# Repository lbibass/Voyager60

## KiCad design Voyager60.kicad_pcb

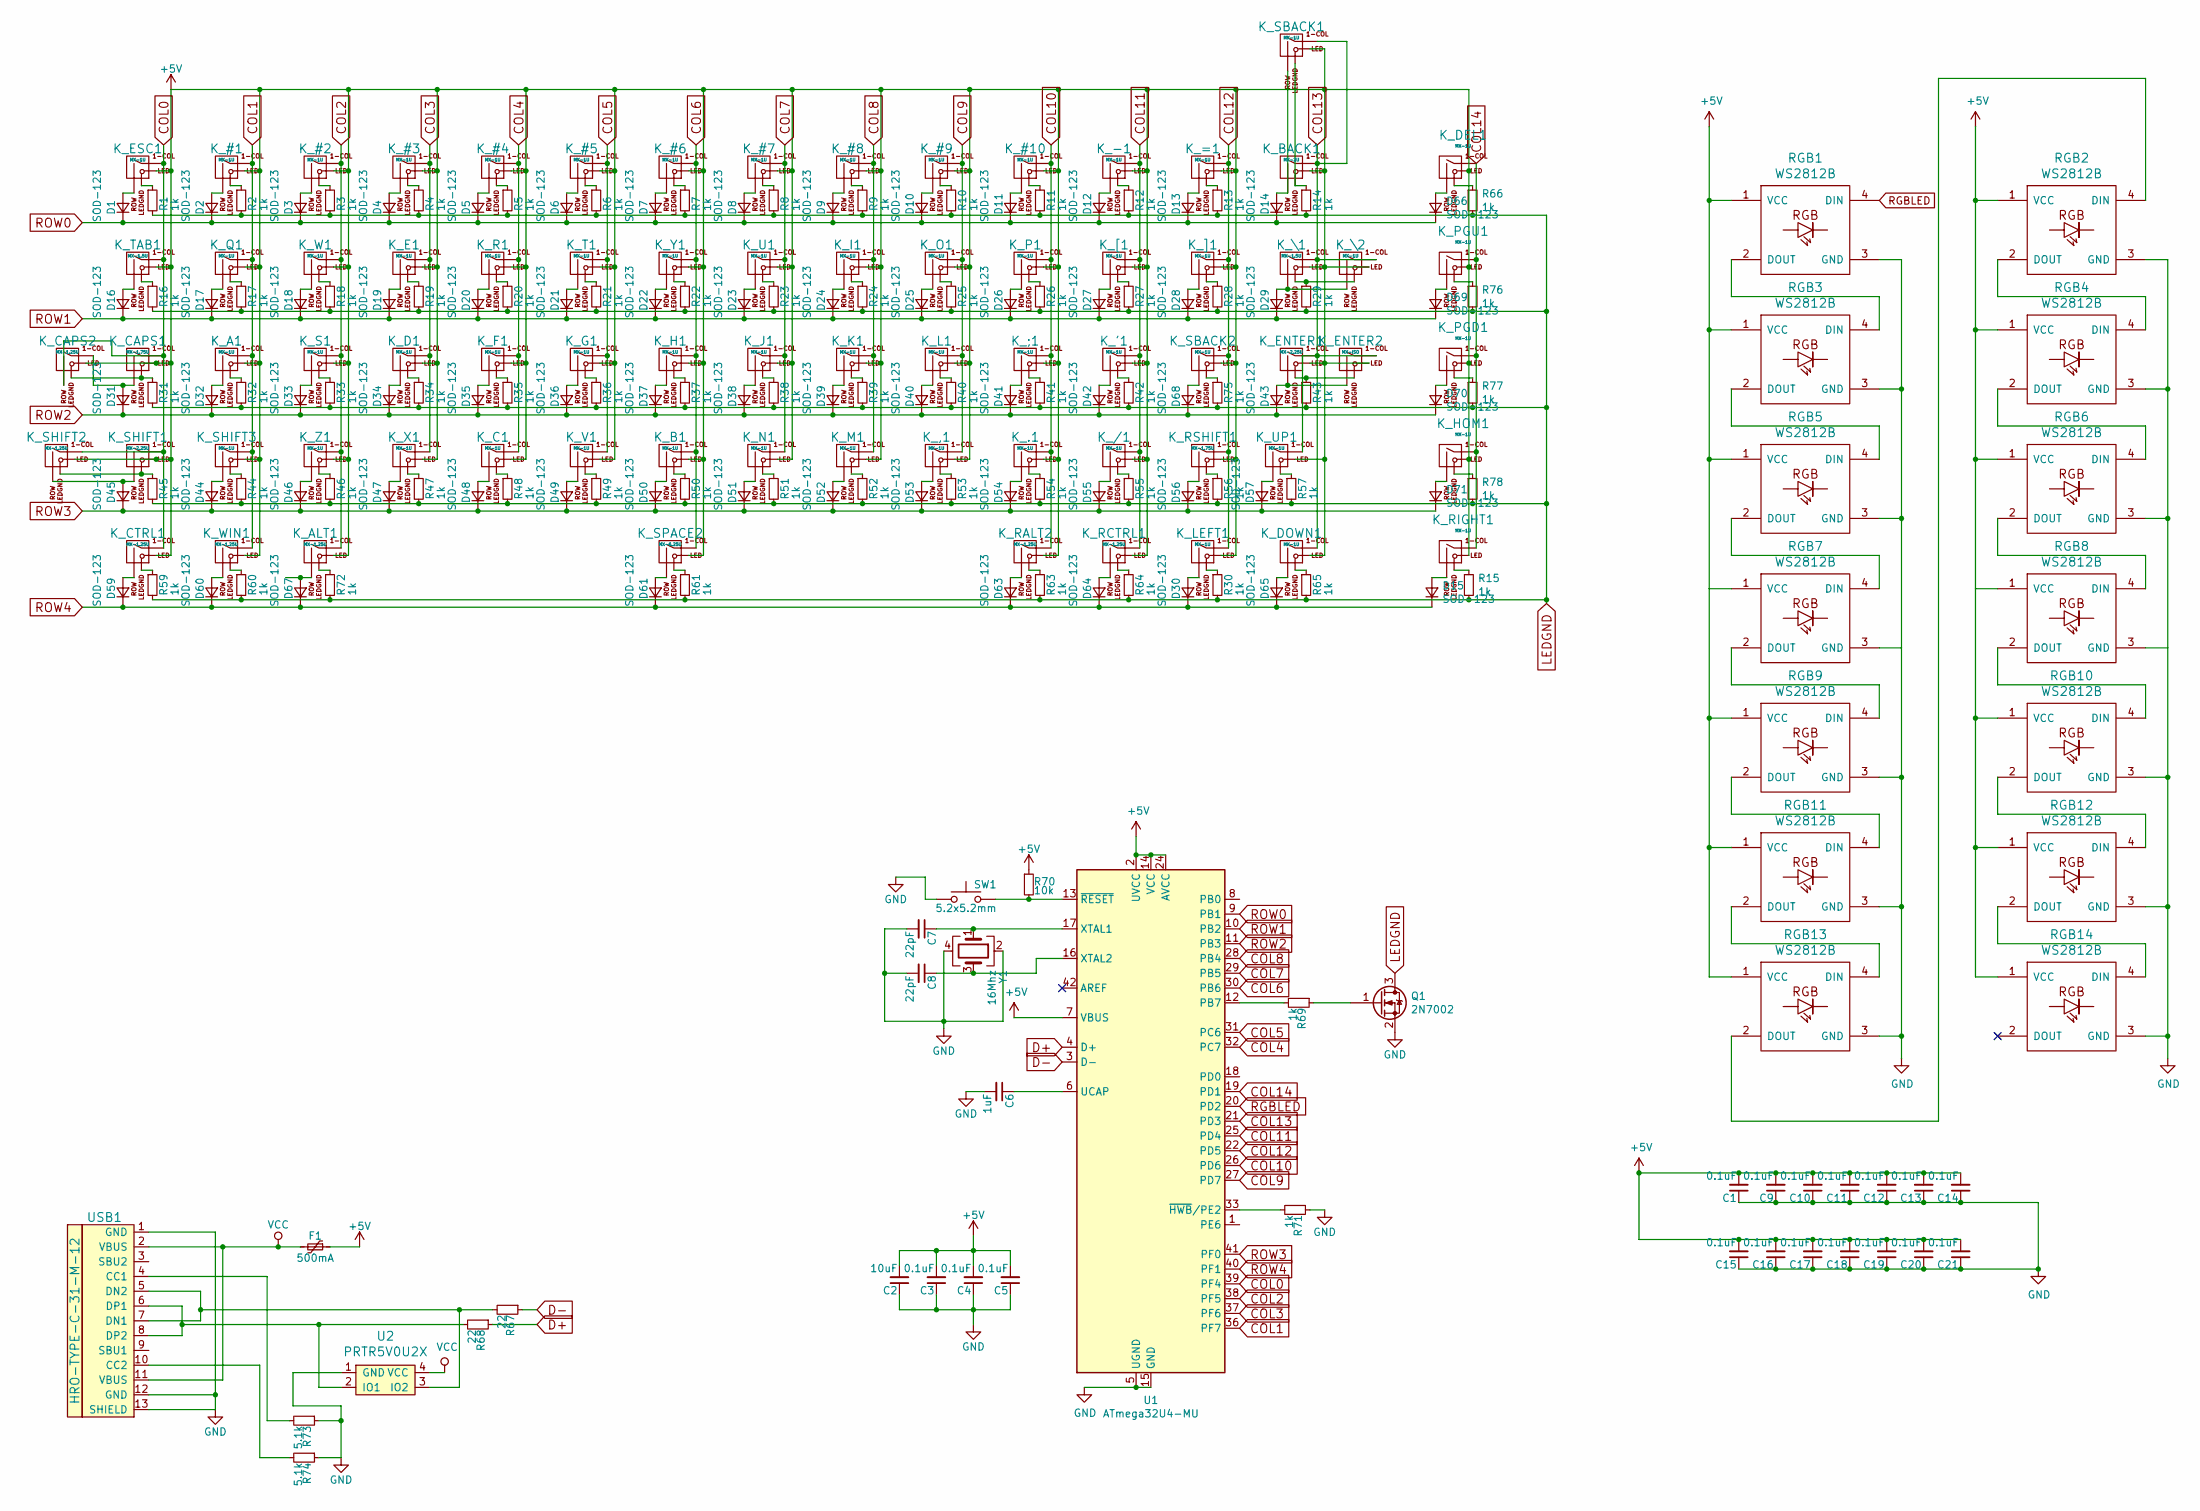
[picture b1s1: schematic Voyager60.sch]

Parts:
C1, C3, C4, C5, C9, C10, C11, C12, C13, C14, C15, C16, C17, C18, C19, C20, C21: 0.1uF; C_0603
C2: 10uF; C_0603
C6: 1uF; C_0603
C7, C8: 22pF; C_0603
D1, D2, D3, D4, D5, D6, D7, D8, D9, D10, D11, D12, D13, D14, D15, D16, D17, D18, D19, D20, D21, D22, D23, D24, D25, D26, D27, D28, D29, D30, D31, D32, D33, D34, D35, D36, D37, D38, D39, D40, D41, D42, D43, D44, D45, D46, D47, D48, D49, D50, D51, D52, D53, D54, D55, D56, D57, D59, D60, D61, D63, D64, D65, D66, D67, D68, D69, D70, D71: SOD-123; D_SOD-123
F1: 500mA; Fuse_SMD1206_Reflow
K_#1, K_#2, K_#3, K_#4, K_#5, K_#6, K_#7, K_#8, K_#9, K_#10: MX-1U
K_'1: MX-1U
K_,1: MX-1U
K_-1: MX-1U
K_.1: MX-1U
K_/1: MX-1U
K_;1: MX-1U
K_=1: MX-1U
K_A1: MX-1U
K_ALT1: MX-1.25U
K_B1: MX-1U
K_BACK1: MX-2U
K_C1: MX-1U
K_CAPS1: MX-1.75U
K_CAPS2: MX-1.25U; MX-1.25U-FLIPPED
K_CTRL1: MX-1.25U
K_D1: MX-1U
K_DEL1: MX-1U
K_DOWN1: MX-1U
K_E1: MX-1U
K_ENTER1: MX-2.25U
K_ENTER2: MX-ISO; MX-ISO-ReversedStabilizers
K_ESC1: MX-1U
K_F1: MX-1U
K_G1: MX-1U
K_H1: MX-1U
K_HOM1: MX-1U
K_I1: MX-1U
K_J1: MX-1U
K_K1: MX-1U
K_L1: MX-1U
K_LEFT1: MX-1U
K_M1: MX-1U
K_N1: MX-1U
K_O1: MX-1U
K_P1: MX-1U
K_PGD1: MX-1U
K_PGU1: MX-1U
K_Q1: MX-1U
K_R1: MX-1U
K_RALT2: MX-1.25U; MX-1.25U-FLIPPED
K_RCTRL1: MX-1.25U
K_RIGHT1: MX-1U
K_RSHIFT1: MX-1.75U
K_S1: MX-1U
K_SBACK1, K_SBACK2: MX-1U
K_SHIFT1: MX-2.25U
K_SHIFT2: MX-1.25U
K_SHIFT3: MX-1U
K_SPACE2: MX-6.25U; MX-6.25U-ReversedStabilizers
K_T1: MX-1U
K_TAB1: MX-1.5U
K_U1: MX-1U
K_UP1: MX-1U
K_V1: MX-1U
K_W1: MX-1U
K_WIN1: MX-1.25U
K_X1: MX-1U
K_Y1: MX-1U
K_Z1: MX-1U
K_[1: MX-1U
K_\1: MX-1.5U
K_\2: MX-1U
K_]1: MX-1U
Q1: 2N7002; SOT-23
R1, R2, R3, R4, R5, R6, R7, R8, R9, R10, R11, R12, R13, R14, R15, R16, R17, R18, R19, R20, R21, R22, R23, R24, R25, R26, R27, R28, R29, R30, R31, R32, R33, R34, R35, R36, R37, R38, R39, R40, R41, R42, R43, R44, R45, R46, R47, R48, R49, R50, R51, R52, R53, R54, R55, R56, R57, R59, R60, R61, R63, R64, R65, R66, R69, R71, R72, R75, R76, R77, R78: 1k; R_0805
R67, R68: 22; R_0805
R70: 10k; R_0805
R73, R74: 5.1k; R_0805
RGB1, RGB2, RGB3, RGB4, RGB5, RGB6, RGB7, RGB8, RGB9, RGB10, RGB11, RGB12, RGB13, RGB14: WS2812B
SW1: 5.2x5.2mm; SKQG-1155865
U1: ATmega32U4-MU; QFN-44-1EP_7x7mm_Pitch0.5mm
U2: PRTR5V0U2X; SOT143B
USB1: HRO-TYPE-C-31-M-12; HRO-TYPE-C-31-M-12-Assembly
Y1: 16Mhz; Crystal_SMD_3225-4pin_3.2x2.5mm

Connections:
+5V: C1.2, C2.2, C3.2, C4.2, C5.2, C9.2, C10.2, C11.2, C12.2, C13.2, C14.2, C15.2, C16.2, C17.2, C18.2, C19.2, C20.2, C21.2, F1.1, K_#1.3 (LED), K_#2.3 (LED), K_#3.3 (LED), K_#4.3 (LED), K_#5.3 (LED), K_#6.3 (LED), K_#7.3 (LED), K_#8.3 (LED), K_#9.3 (LED), K_#10.3 (LED), K_'1.3 (LED), K_,1.3 (LED), K_-1.3 (LED), K_.1.3 (LED), K_/1.3 (LED), K_;1.3 (LED), K_=1.3 (LED), K_A1.3 (LED), K_ALT1.3 (LED), K_B1.3 (LED), K_BACK1.3 (LED), K_C1.3 (LED), K_CAPS1.3 (LED), K_CAPS2.3 (LED), K_CTRL1.3 (LED), K_D1.3 (LED), K_DEL1.3 (LED), K_DOWN1.3 (LED), K_E1.3 (LED), K_ENTER1.3 (LED), K_ENTER2.3 (LED), K_ESC1.3 (LED), K_F1.3 (LED), K_G1.3 (LED), K_H1.3 (LED), K_HOM1.3 (LED), K_I1.3 (LED), K_J1.3 (LED), K_K1.3 (LED), K_L1.3 (LED), K_LEFT1.3 (LED), K_M1.3 (LED), K_N1.3 (LED), K_O1.3 (LED), K_P1.3 (LED), K_PGD1.3 (LED), K_PGU1.3 (LED), K_Q1.3 (LED), K_R1.3 (LED), K_RALT2.3 (LED), K_RCTRL1.3 (LED), K_RIGHT1.3 (LED), K_RSHIFT1.3 (LED), K_S1.3 (LED), K_SBACK1.3 (LED), K_SBACK2.3 (LED), K_SHIFT1.3 (LED), K_SHIFT2.3 (LED), K_SHIFT3.3 (LED), K_SPACE2.3 (LED), K_T1.3 (LED), K_TAB1.3 (LED), K_U1.3 (LED), K_UP1.3 (LED), K_V1.3 (LED), K_W1.3 (LED), K_WIN1.3 (LED), K_X1.3 (LED), K_Y1.3 (LED), K_Z1.3 (LED), K_[1.3 (LED), K_\1.3 (LED), K_\2.3 (LED), K_]1.3 (LED), R70.1, RGB1.1 (VCC), RGB2.1 (VCC), RGB3.1 (VCC), RGB4.1 (VCC), RGB5.1 (VCC), RGB6.1 (VCC), RGB7.1 (VCC), RGB8.1 (VCC), RGB9.1 (VCC), RGB10.1 (VCC), RGB11.1 (VCC), RGB12.1 (VCC), RGB13.1 (VCC), RGB14.1 (VCC), U1.2 (UVCC), U1.7 (VBUS), U1.14 (VCC), U1.24 (AVCC), U1.34 (VCC), U1.44 (AVCC)
COL0: K_CAPS1.1 (COL), K_CAPS2.2 (ROW), K_CTRL1.1 (COL), K_ESC1.1 (COL), K_SHIFT1.1 (COL), K_SHIFT2.1 (COL), K_TAB1.1 (COL), U1.39 (PF4)
COL1: K_#1.1 (COL), K_A1.1 (COL), K_Q1.1 (COL), K_SHIFT3.1 (COL), K_WIN1.1 (COL), U1.36 (PF7)
COL2: K_#2.1 (COL), K_ALT1.1 (COL), K_S1.1 (COL), K_W1.1 (COL), K_Z1.1 (COL), U1.38 (PF5)
COL3: K_#3.1 (COL), K_D1.1 (COL), K_E1.1 (COL), K_X1.1 (COL), U1.37 (PF6)
COL4: K_#4.1 (COL), K_C1.1 (COL), K_F1.1 (COL), K_R1.1 (COL), U1.32 (PC7)
COL5: K_#5.1 (COL), K_G1.1 (COL), K_T1.1 (COL), K_V1.1 (COL), U1.31 (PC6)
COL6: K_#6.1 (COL), K_B1.1 (COL), K_H1.1 (COL), K_SPACE2.1 (COL), K_Y1.1 (COL), U1.30 (PB6)
COL7: K_#7.1 (COL), K_J1.1 (COL), K_N1.1 (COL), K_U1.1 (COL), U1.29 (PB5)
COL8: K_#8.1 (COL), K_I1.1 (COL), K_K1.1 (COL), K_M1.1 (COL), U1.28 (PB4)
COL9: K_#9.1 (COL), K_,1.1 (COL), K_L1.1 (COL), K_O1.1 (COL), U1.27 (PD7)
COL10: K_#10.1 (COL), K_.1.1 (COL), K_;1.1 (COL), K_P1.1 (COL), K_RALT2.1 (COL), U1.26 (PD6)
COL11: K_'1.1 (COL), K_-1.1 (COL), K_/1.1 (COL), K_RCTRL1.1 (COL), K_[1.1 (COL), U1.25 (PD4)
COL12: K_=1.1 (COL), K_LEFT1.1 (COL), K_RSHIFT1.1 (COL), K_SBACK2.1 (COL), K_]1.1 (COL), U1.22 (PD5)
COL13: K_BACK1.1 (COL), K_DOWN1.1 (COL), K_ENTER1.1 (COL), K_ENTER2.1 (COL), K_SBACK1.1 (COL), K_UP1.1 (COL), K_\1.1 (COL), K_\2.1 (COL), U1.21 (PD3)
COL14: K_DEL1.1 (COL), K_HOM1.1 (COL), K_PGD1.1 (COL), K_PGU1.1 (COL), K_RIGHT1.1 (COL), U1.19 (PD1)
D+: R68.1, U1.4 (D+)
D-: R67.1, U1.3 (D-)
GND: C1.1, C2.1, C3.1, C4.1, C5.1, C6.2, C7.2, C8.2, C9.1, C10.1, C11.1, C12.1, C13.1, C14.1, C15.1, C16.1, C17.1, C18.1, C19.1, C20.1, C21.1, Q1.2 (S), R71.1, R73.1, R74.1, RGB1.3 (GND), RGB2.3 (GND), RGB3.3 (GND), RGB4.3 (GND), RGB5.3 (GND), RGB6.3 (GND), RGB7.3 (GND), RGB8.3 (GND), RGB9.3 (GND), RGB10.3 (GND), RGB11.3 (GND), RGB12.3 (GND), RGB13.3 (GND), RGB14.3 (GND), SW1.1, U1.5 (UGND), U1.15 (GND), U1.23 (GND), U1.35 (GND), U1.43 (GND), U1.45 (GND), U2.1 (GND), USB1.1 (GND), USB1.12 (GND), USB1.13 (SHIELD), Y1.2, Y1.4
LEDGND: Q1.3 (D), R1.2, R2.2, R3.2, R4.2, R5.2, R6.2, R7.2, R8.2, R9.2, R10.2, R11.2, R12.2, R13.2, R14.2, R15.2, R16.2, R17.2, R18.2, R19.2, R20.2, R21.2, R22.2, R23.2, R24.2, R25.2, R26.2, R27.2, R28.2, R29.2, R30.2, R31.2, R32.2, R33.2, R34.2, R35.2, R36.2, R37.2, R38.2, R39.2, R40.2, R41.2, R42.2, R43.2, R44.2, R45.2, R46.2, R47.2, R48.2, R49.2, R50.2, R51.2, R52.2, R53.2, R54.2, R55.2, R56.2, R57.2, R59.2, R60.2, R61.2, R63.2, R64.2, R65.2, R66.2, R72.2, R75.2, R76.2, R77.2, R78.2
unnamed: C6.1, U1.6 (UCAP)
unnamed: C7.1, U1.17 (XTAL1), Y1.1
unnamed: C8.1, U1.16 (XTAL2), Y1.3
unnamed: D1.2 (A), K_ESC1.2 (ROW)
unnamed: D2.2 (A), K_#1.2 (ROW)
unnamed: D3.2 (A), K_#2.2 (ROW)
unnamed: D4.2 (A), K_#3.2 (ROW)
unnamed: D5.2 (A), K_#4.2 (ROW)
unnamed: D6.2 (A), K_#5.2 (ROW)
unnamed: D7.2 (A), K_#6.2 (ROW)
unnamed: D8.2 (A), K_#7.2 (ROW)
unnamed: D9.2 (A), K_#8.2 (ROW)
unnamed: D10.2 (A), K_#9.2 (ROW)
unnamed: D11.2 (A), K_#10.2 (ROW)
unnamed: D12.2 (A), K_-1.2 (ROW)
unnamed: D13.2 (A), K_=1.2 (ROW)
unnamed: D14.2 (A), K_BACK1.2 (ROW), K_SBACK1.2 (ROW)
unnamed: D15.2 (A), K_RIGHT1.2 (ROW)
unnamed: D16.2 (A), K_TAB1.2 (ROW)
unnamed: D17.2 (A), K_Q1.2 (ROW)
unnamed: D18.2 (A), K_W1.2 (ROW)
unnamed: D19.2 (A), K_E1.2 (ROW)
unnamed: D20.2 (A), K_R1.2 (ROW)
unnamed: D21.2 (A), K_T1.2 (ROW)
unnamed: D22.2 (A), K_Y1.2 (ROW)
unnamed: D23.2 (A), K_U1.2 (ROW)
unnamed: D24.2 (A), K_I1.2 (ROW)
unnamed: D25.2 (A), K_O1.2 (ROW)
unnamed: D26.2 (A), K_P1.2 (ROW)
unnamed: D27.2 (A), K_[1.2 (ROW)
unnamed: D28.2 (A), K_]1.2 (ROW)
unnamed: D29.2 (A), K_\1.2 (ROW), K_\2.2 (ROW)
unnamed: D30.2 (A), K_LEFT1.2 (ROW)
unnamed: D31.2 (A), K_CAPS1.2 (ROW), K_CAPS2.1 (COL)
unnamed: D32.2 (A), K_A1.2 (ROW)
unnamed: D33.2 (A), K_S1.2 (ROW)
unnamed: D34.2 (A), K_D1.2 (ROW)
unnamed: D35.2 (A), K_F1.2 (ROW)
unnamed: D36.2 (A), K_G1.2 (ROW)
unnamed: D37.2 (A), K_H1.2 (ROW)
unnamed: D38.2 (A), K_J1.2 (ROW)
unnamed: D39.2 (A), K_K1.2 (ROW)
unnamed: D40.2 (A), K_L1.2 (ROW)
unnamed: D41.2 (A), K_;1.2 (ROW)
unnamed: D42.2 (A), K_'1.2 (ROW)
unnamed: D43.2 (A), K_ENTER1.2 (ROW), K_ENTER2.2 (ROW)
unnamed: D44.2 (A), K_SHIFT3.2 (ROW)
unnamed: D45.2 (A), K_SHIFT1.2 (ROW), K_SHIFT2.2 (ROW)
unnamed: D46.2 (A), K_Z1.2 (ROW)
unnamed: D47.2 (A), K_X1.2 (ROW)
unnamed: D48.2 (A), K_C1.2 (ROW)
unnamed: D49.2 (A), K_V1.2 (ROW)
unnamed: D50.2 (A), K_B1.2 (ROW)
unnamed: D51.2 (A), K_N1.2 (ROW)
unnamed: D52.2 (A), K_M1.2 (ROW)
unnamed: D53.2 (A), K_,1.2 (ROW)
unnamed: D54.2 (A), K_.1.2 (ROW)
unnamed: D55.2 (A), K_/1.2 (ROW)
unnamed: D56.2 (A), K_RSHIFT1.2 (ROW)
unnamed: D57.2 (A), K_UP1.2 (ROW)
unnamed: D59.2 (A), K_CTRL1.2 (ROW)
unnamed: D60.2 (A), K_WIN1.2 (ROW)
unnamed: D61.2 (A), K_SPACE2.2 (ROW)
unnamed: D63.2 (A), K_RALT2.2 (ROW)
unnamed: D64.2 (A), K_RCTRL1.2 (ROW)
unnamed: D65.2 (A), K_DOWN1.2 (ROW)
unnamed: D66.2 (A), K_DEL1.2 (ROW)
unnamed: D67.2 (A), K_ALT1.2 (ROW)
unnamed: D68.2 (A), K_SBACK2.2 (ROW)
unnamed: D69.2 (A), K_PGU1.2 (ROW)
unnamed: D70.2 (A), K_PGD1.2 (ROW)
unnamed: D71.2 (A), K_HOM1.2 (ROW)
unnamed: K_#1.4 (LEDGND), R2.1
unnamed: K_#2.4 (LEDGND), R3.1
unnamed: K_#3.4 (LEDGND), R4.1
unnamed: K_#4.4 (LEDGND), R5.1
unnamed: K_#5.4 (LEDGND), R6.1
unnamed: K_#6.4 (LEDGND), R7.1
unnamed: K_#7.4 (LEDGND), R8.1
unnamed: K_#8.4 (LEDGND), R9.1
unnamed: K_#9.4 (LEDGND), R10.1
unnamed: K_#10.4 (LEDGND), R11.1
unnamed: K_'1.4 (LEDGND), R42.1
unnamed: K_,1.4 (LEDGND), R53.1
unnamed: K_-1.4 (LEDGND), R12.1
unnamed: K_.1.4 (LEDGND), R54.1
unnamed: K_/1.4 (LEDGND), R55.1
unnamed: K_;1.4 (LEDGND), R41.1
unnamed: K_=1.4 (LEDGND), R13.1
unnamed: K_A1.4 (LEDGND), R32.1
unnamed: K_ALT1.4 (LEDGND), R72.1
unnamed: K_B1.4 (LEDGND), R50.1
unnamed: K_BACK1.4 (LEDGND), K_SBACK1.4 (LEDGND), R14.1
unnamed: K_C1.4 (LEDGND), R48.1
unnamed: K_CAPS1.4 (LEDGND), K_CAPS2.4 (LEDGND), R31.1
unnamed: K_CTRL1.4 (LEDGND), R59.1
unnamed: K_D1.4 (LEDGND), R34.1
unnamed: K_DEL1.4 (LEDGND), R66.1
unnamed: K_DOWN1.4 (LEDGND), R65.1
unnamed: K_E1.4 (LEDGND), R19.1
unnamed: K_ENTER1.4 (LEDGND), K_ENTER2.4 (LEDGND), R43.1
unnamed: K_ESC1.4 (LEDGND), R1.1
unnamed: K_F1.4 (LEDGND), R35.1
unnamed: K_G1.4 (LEDGND), R36.1
unnamed: K_H1.4 (LEDGND), R37.1
unnamed: K_HOM1.4 (LEDGND), R78.1
unnamed: K_I1.4 (LEDGND), R24.1
unnamed: K_J1.4 (LEDGND), R38.1
unnamed: K_K1.4 (LEDGND), R39.1
unnamed: K_L1.4 (LEDGND), R40.1
unnamed: K_LEFT1.4 (LEDGND), R30.1
unnamed: K_M1.4 (LEDGND), R52.1
unnamed: K_N1.4 (LEDGND), R51.1
unnamed: K_O1.4 (LEDGND), R25.1
unnamed: K_P1.4 (LEDGND), R26.1
unnamed: K_PGD1.4 (LEDGND), R77.1
unnamed: K_PGU1.4 (LEDGND), R76.1
unnamed: K_Q1.4 (LEDGND), R17.1
unnamed: K_R1.4 (LEDGND), R20.1
unnamed: K_RALT2.4 (LEDGND), R63.1
unnamed: K_RCTRL1.4 (LEDGND), R64.1
unnamed: K_RIGHT1.4 (LEDGND), R15.1
unnamed: K_RSHIFT1.4 (LEDGND), R56.1
unnamed: K_S1.4 (LEDGND), R33.1
unnamed: K_SBACK2.4 (LEDGND), R75.1
unnamed: K_SHIFT1.4 (LEDGND), K_SHIFT2.4 (LEDGND), R45.1
unnamed: K_SHIFT3.4 (LEDGND), R44.1
unnamed: K_SPACE2.4 (LEDGND), R61.1
unnamed: K_T1.4 (LEDGND), R21.1
unnamed: K_TAB1.4 (LEDGND), R16.1
unnamed: K_U1.4 (LEDGND), R23.1
unnamed: K_UP1.4 (LEDGND), R57.1
unnamed: K_V1.4 (LEDGND), R49.1
unnamed: K_W1.4 (LEDGND), R18.1
unnamed: K_WIN1.4 (LEDGND), R60.1
unnamed: K_X1.4 (LEDGND), R47.1
unnamed: K_Y1.4 (LEDGND), R22.1
unnamed: K_Z1.4 (LEDGND), R46.1
unnamed: K_[1.4 (LEDGND), R27.1
unnamed: K_\1.4 (LEDGND), K_\2.4 (LEDGND), R29.1
unnamed: K_]1.4 (LEDGND), R28.1
unnamed: Q1.1 (G), R69.1
unnamed: R67.2, U2.3 (IO2), USB1.5 (DN2), USB1.7 (DN1)
unnamed: R68.2, U2.2 (IO1), USB1.6 (DP1), USB1.8 (DP2)
unnamed: R69.2, U1.12 (PB7)
unnamed: R70.2, SW1.2, U1.13 (~RESET)
unnamed: R71.2, U1.33 (~HWB~/PE2)
unnamed: R73.2, USB1.4 (CC1)
unnamed: R74.2, USB1.10 (CC2)
unnamed: RGB1.2 (DOUT), RGB3.4 (DIN)
unnamed: RGB2.2 (DOUT), RGB4.4 (DIN)
unnamed: RGB3.2 (DOUT), RGB5.4 (DIN)
unnamed: RGB4.2 (DOUT), RGB6.4 (DIN)
unnamed: RGB5.2 (DOUT), RGB7.4 (DIN)
unnamed: RGB6.2 (DOUT), RGB8.4 (DIN)
unnamed: RGB7.2 (DOUT), RGB9.4 (DIN)
unnamed: RGB10.2 (DOUT), RGB12.4 (DIN)
unnamed: RGB8.2 (DOUT), RGB10.4 (DIN)
unnamed: RGB11.2 (DOUT), RGB13.4 (DIN)
unnamed: RGB9.2 (DOUT), RGB11.4 (DIN)
unnamed: RGB12.2 (DOUT), RGB14.4 (DIN)
unnamed: RGB2.4 (DIN), RGB13.2 (DOUT)
RGBLED: RGB1.4 (DIN), U1.20 (PD2)
ROW0: D1.1 (K), D2.1 (K), D3.1 (K), D4.1 (K), D5.1 (K), D6.1 (K), D7.1 (K), D8.1 (K), D9.1 (K), D10.1 (K), D11.1 (K), D12.1 (K), D13.1 (K), D14.1 (K), D66.1 (K), U1.9 (PB1)
ROW1: D16.1 (K), D17.1 (K), D18.1 (K), D19.1 (K), D20.1 (K), D21.1 (K), D22.1 (K), D23.1 (K), D24.1 (K), D25.1 (K), D26.1 (K), D27.1 (K), D28.1 (K), D29.1 (K), D69.1 (K), U1.10 (PB2)
ROW2: D31.1 (K), D32.1 (K), D33.1 (K), D34.1 (K), D35.1 (K), D36.1 (K), D37.1 (K), D38.1 (K), D39.1 (K), D40.1 (K), D41.1 (K), D42.1 (K), D43.1 (K), D68.1 (K), D70.1 (K), U1.11 (PB3)
ROW3: D44.1 (K), D45.1 (K), D46.1 (K), D47.1 (K), D48.1 (K), D49.1 (K), D50.1 (K), D51.1 (K), D52.1 (K), D53.1 (K), D54.1 (K), D55.1 (K), D56.1 (K), D57.1 (K), D71.1 (K), U1.41 (PF0)
ROW4: D15.1 (K), D30.1 (K), D59.1 (K), D60.1 (K), D61.1 (K), D63.1 (K), D64.1 (K), D65.1 (K), D67.1 (K), U1.40 (PF1)
VCC: F1.2, U2.4 (VCC), USB1.2 (VBUS), USB1.11 (VBUS)

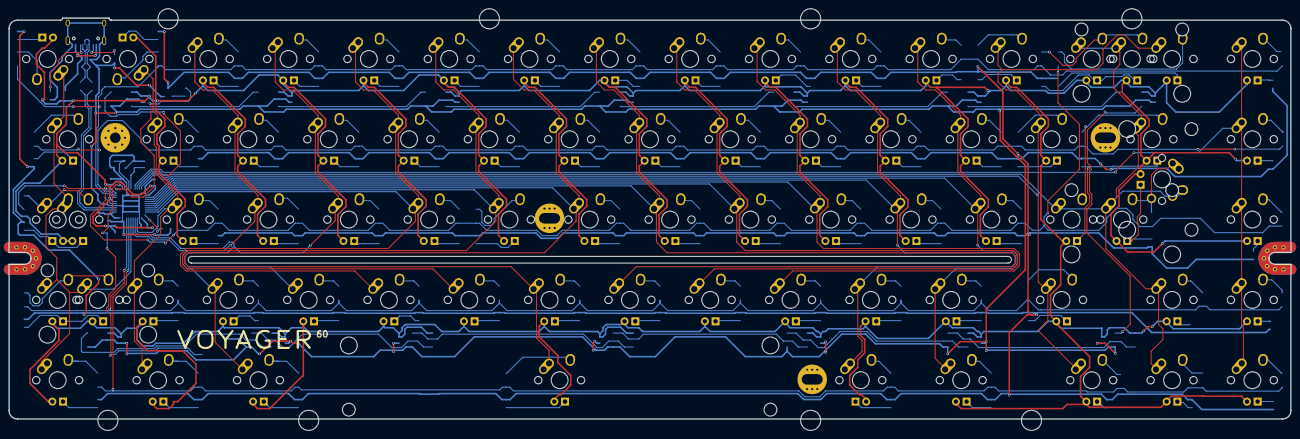
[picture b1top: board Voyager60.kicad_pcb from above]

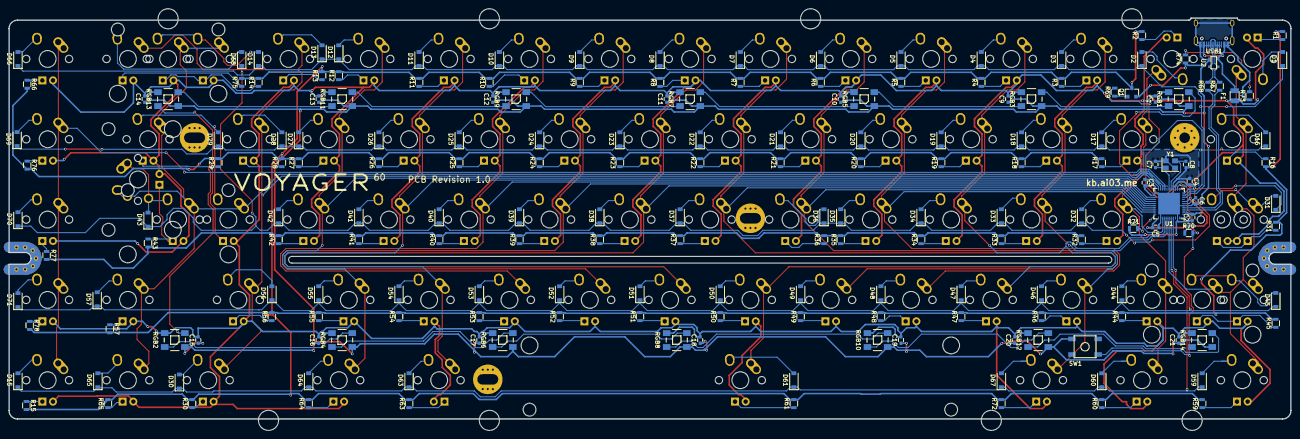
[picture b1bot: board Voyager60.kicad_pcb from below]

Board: 2 copper layers, 304.0 x 100.0 mm, 261 parts (187 on the bottom side), 189 nets.

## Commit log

2019-02-25 Alps Stepped Caps Lock
    Added alps stepped caps lock support at the cost of removing caps lock LED support.
2020-01-04 65% variant of voyager60
